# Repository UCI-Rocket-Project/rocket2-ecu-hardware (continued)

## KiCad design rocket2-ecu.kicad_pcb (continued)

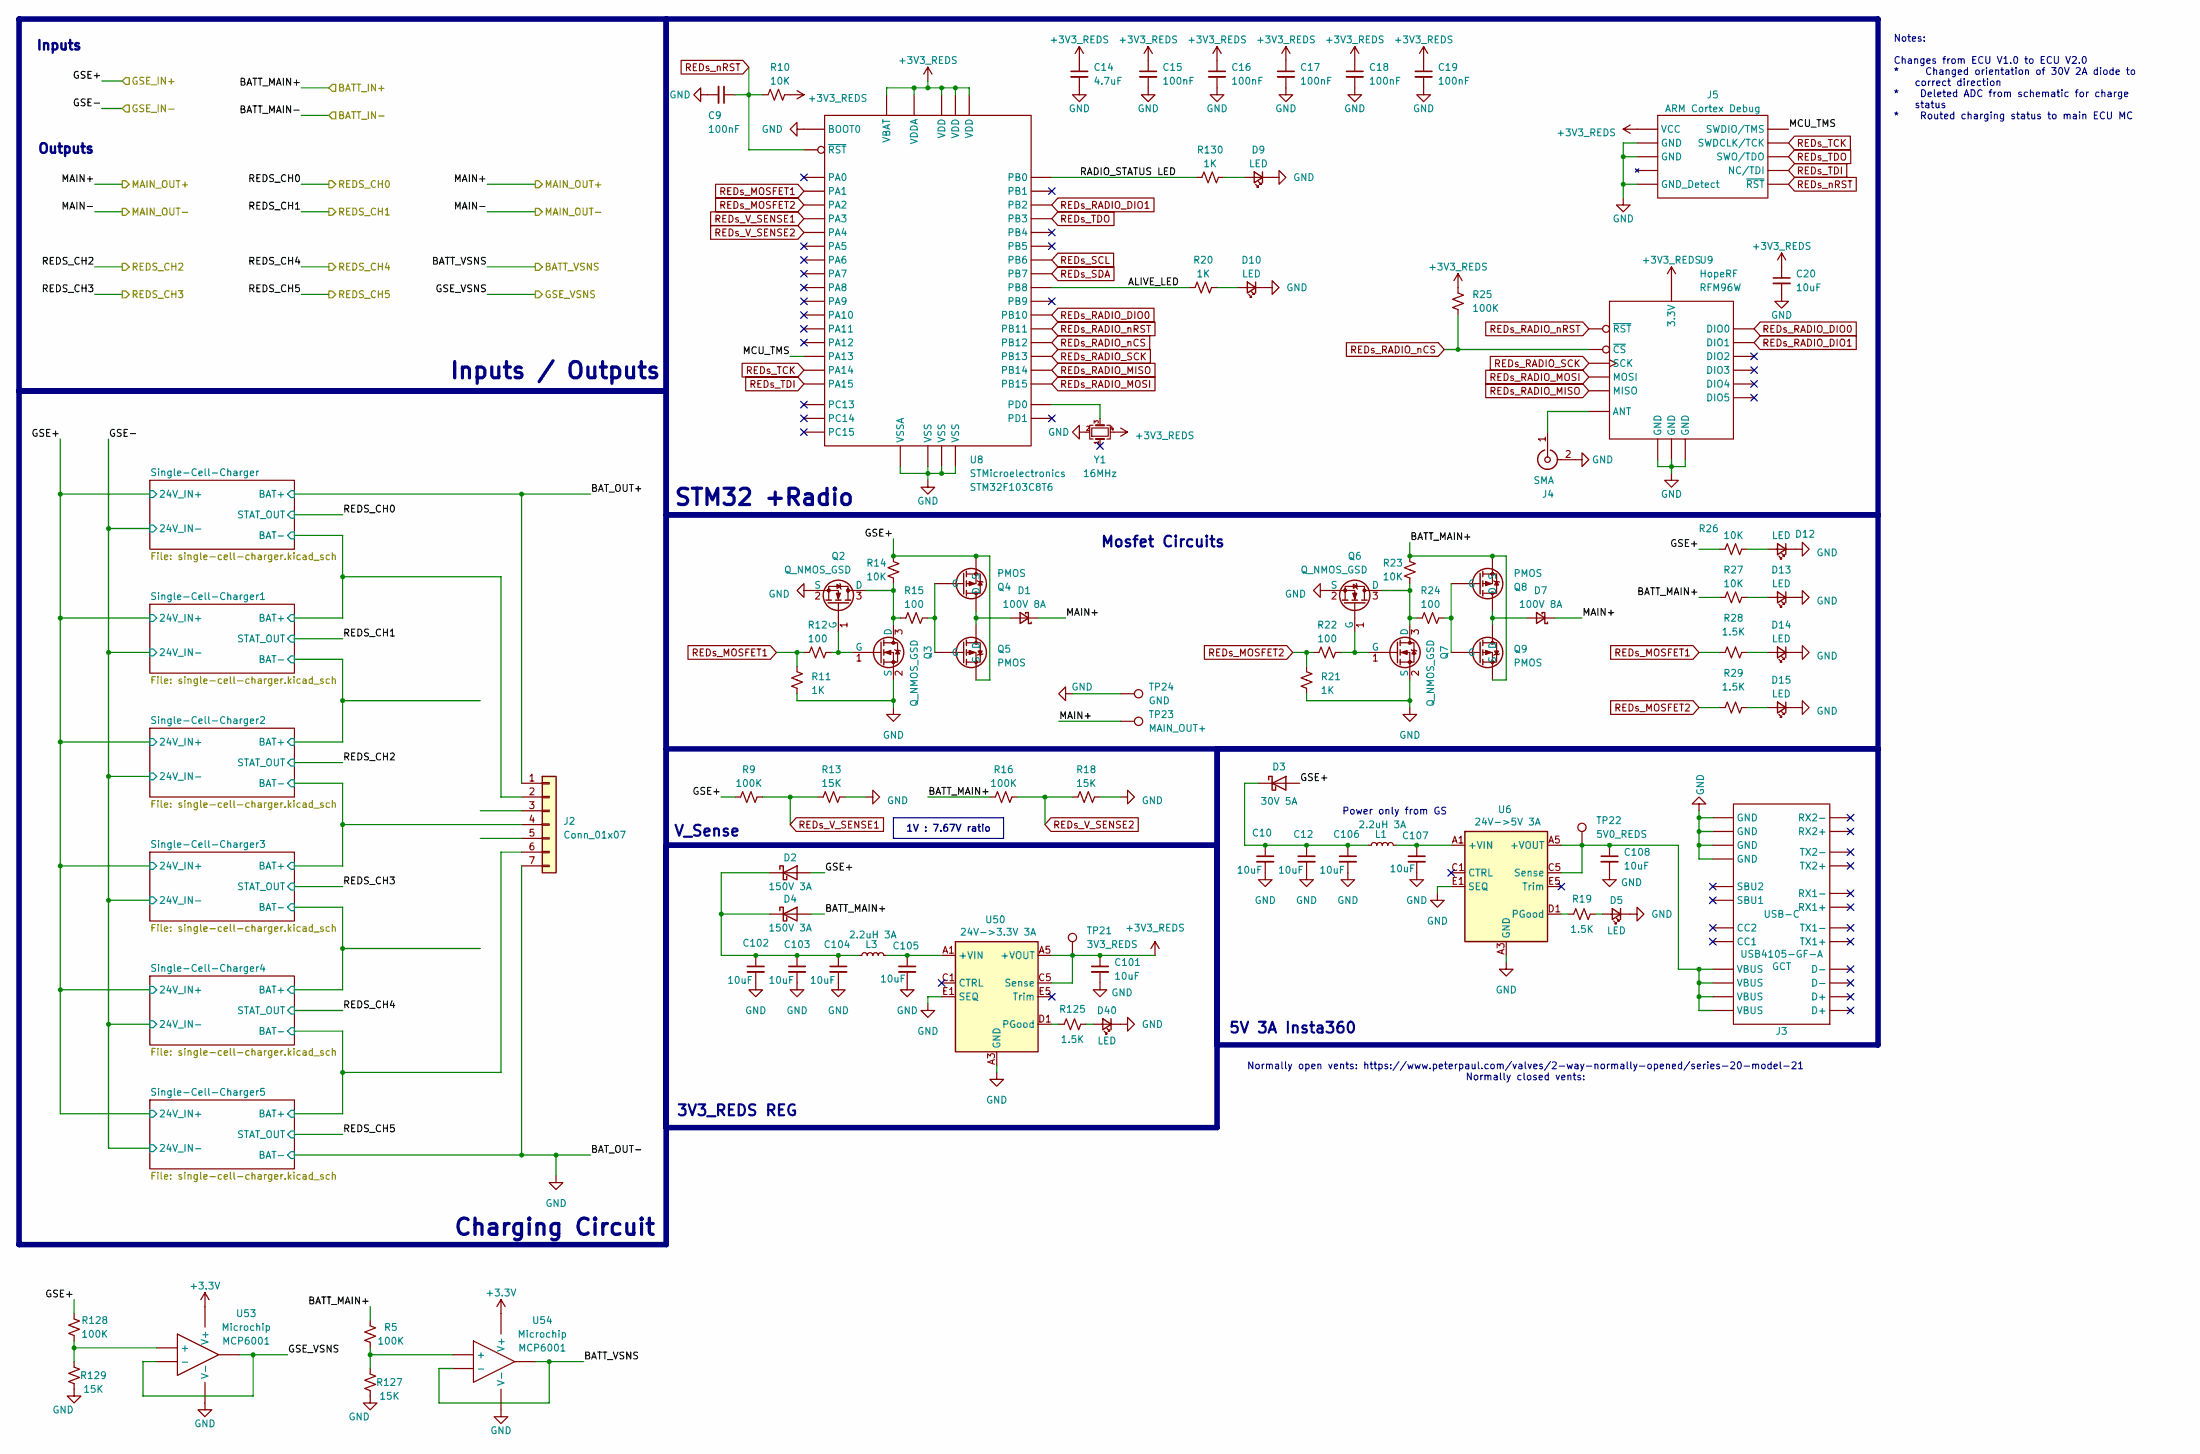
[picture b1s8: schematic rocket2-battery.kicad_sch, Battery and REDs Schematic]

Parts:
C9, C15, C16, C17, C18, C19: 100nF; C_0402_1005Metric; Part # Generic CAP CER 0.1UF 6.3V X7R 0402
C10, C12, C102, C103, C104, C105, C106, C107: 10uF; C_1210_3225Metric; Part # Generic CAP CER 10UF 50V X7R 1210
C14: 4.7uF; C_0603_1608Metric; Part # Generic CAP CER 4.7UF 6.3V X7R 0603
C20: 10uF; C_0603_1608Metric; Part # Generic CAP CER 10UF 50V X7R 0603
C101, C108: 10uF; C_1206_3216Metric; Part # Generic CAP CER 10UF 25V X7R 1206
D1, D7: 100V 8A; D_PowerDI-5; Part # SDT8A100P5-7
D2, D4: 150V 3A; D_SMF
D3: 30V 5A; D_SOD-128; Part # PMEG3050EP,115
D5, D40: LED; LED_0603_1608Metric_Pad1.05x0.95mm_HandSolder; Part # Generic 0603 Yellow-Green LED
D9, D10, D14, D15: LED; LED_0603_1608Metric_Pad1.05x0.95mm_HandSolder; Part # Generic 0603 Red LED
D12, D13: LED; LED_0603_1608Metric_Pad1.05x0.95mm_HandSolder; Part # Generic 0603 Green LED
J2: Conn_01x07; JST_PH_B7B-PH-K_1x07_P2.00mm_Vertical; Part # Generic 2.54mm 1x7 Pin Header
J3: USB-C; USB_C_Receptacle_GCT_USB4105-xx-A_16P_TopMnt_Horizontal; Part # USB4105-GF-A
J4: SMA; SMA_Molex_73251-2200_Horizontal; Part # 0732512200
J5: ARM Cortex Debug; PinHeader_2x05_P1.27mm_Vertical_SMD; Part # Generic 1.27mm 2x5 Pin Header
L1, L3: 2.2uH 3A; L_Vishay_IHLP-1212; Part # IHLP1212BZER2R2M11
Q2, Q3, Q6, Q7: Q_NMOS_GSD; SOT-23-3; Part # NTR4003NT3G
Q4, Q5, Q8, Q9: PMOS; Vishay_PowerPAK_1212-8_Single; Part # SI7315DN-T1-GE3
R5, R9, R16, R25, R128: 100K; R_0402_1005Metric; Part # Generic RES SMD 100K OHM 1% 1/16W 0402
R10, R14, R23, R26, R27: 10K; R_0402_1005Metric; Part # Generic RES SMD 10K OHM 1% 1/4W 0402
R11, R20, R21, R130: 1K; R_0402_1005Metric; Part # Generic RES SMD 1K OHM 1% 1/16W 0402
R12, R15, R22, R24: 100; R_0402_1005Metric; Part # Generic RES SMD 100 OHM 1% 1/4W 0402
R13, R18, R127, R129: 15K; R_0402_1005Metric; Part # Generic RES SMD 15K OHM 0.1% 1/16W 0402
R19, R28, R29, R125: 1.5K; R_0402_1005Metric; Part # Generic RES SMD 1.5K OHM 0.1% 1/16W 0402
TP21: 3V3_REDS; TestPoint_Plated_Hole_D2.0mm
TP22: 5V0_REDS; TestPoint_Plated_Hole_D2.0mm
TP23: MAIN_OUT+; TestPoint_Plated_Hole_D2.0mm
TP24: GND; TestPoint_Plated_Hole_D2.0mm
U6: 24V->5V 3A; Converter_DCDC_RECOM_RPMx.x-x.0; Part # RPMB5.0-3.0
U8: LQFP-48_7x7mm_P0.5mm; Part # STM32F103C8T6
U9: RFM95W; Part # RFM96W
U50: 24V->3.3V 3A; Converter_DCDC_RECOM_RPMx.x-x.0; Part # RPMB3.3-3.0
U53, U54: SOT-23-5; Part # MCP6001
Y1: 16MHz; Crystal_SMD_2520-4Pin_2.5x2.0mm; Part # ECS-2520MV-160-CN

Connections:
+3.3V: U53.5 (V+), U54.5 (V+); also elsewhere on the board
+3V3_REDS: C14.1, C15.1, C16.1, C17.1, C18.1, C19.1, C20.1, C101.1, J5.1 (VCC), R10.1, R25.1, TP21.1, U8.1 (VBAT), U8.9 (VDDA), U8.24 (VDD), U8.36 (VDD), U8.48 (VDD), U9.13 (3.3V), U50.A5 (+VOUT), U50.B5 (+VOUT), U50.C5 (Sense), Y1.4; also elsewhere on the board
+24V: D1.1 (K), D7.1 (K), TP23.1; also elsewhere on the board
/BATT: D4.2 (A), Q8.1 (S), Q8.2 (S), Q8.3 (S), Q9.1 (S), Q9.2 (S), Q9.3 (S), R5.1, R16.1, R23.1, R27.1; also elsewhere on the board
/GSE: D2.2 (A), D3.2 (A), Q4.1 (S), Q4.2 (S), Q4.3 (S), Q5.1 (S), Q5.2 (S), Q5.3 (S), R9.1, R14.1, R26.1, R128.1; also elsewhere on the board
/REDs/ALIVE_LED: R20.1, U8.45 (PB8)
/REDs/BATT_VSNS: U54.1, U54.4 (-)
/REDs/BAT_OUT+: J2.1; also elsewhere on the board
/REDs/GSE_VSNS: U53.1, U53.4 (-)
/REDs/MCU_TMS: J5.2 (SWDIO/TMS), U8.34 (PA13)
/REDs/RADIO_STATUS LED: R130.1, U8.18 (PB0)
/REDs/Single-Cell-Charger2/ISO_GND: J2.4; also elsewhere on the board
/REDs/Single-Cell-Charger4/ISO_GND: J2.6; also elsewhere on the board
/REDs/Single-Cell-Charger/ISO_GND: J2.2; also elsewhere on the board
GND: C9.2, C10.2, C12.2, C14.2, C15.2, C16.2, C17.2, C18.2, C19.2, C20.2, C101.2, C102.2, C103.2, C104.2, C105.2, C106.2, C107.2, C108.2, D5.1 (K), D9.1 (K), D10.1 (K), D12.1 (K), D13.1 (K), D14.1 (K), D15.1 (K), D40.1 (K), J2.7, J3.A1 (GND), J3.A12 (GND), J3.B1 (GND), J3.B12 (GND), J4.2 (Ext), J5.3 (GND), J5.5 (GND), J5.9 (GND_Detect), Q2.2 (S), Q3.2 (S), Q6.2 (S), Q7.2 (S), R11.1, R13.2, R18.2, R21.1, R127.2, R129.2, TP24.1, U6.A3 (GND), U6.A4 (GND), U6.B1 (GND), U6.B2 (GND), U6.B3 (GND), U6.B4 (GND), U6.C2 (GND), U6.C3 (GND), U6.C4 (GND), U6.D2 (GND), U6.D3 (GND), U6.D4 (GND), U6.D5 (GND), U6.E1 (SEQ), U6.E3 (GND), U6.E4 (GND), U8.8 (VSSA), U8.23 (VSS), U8.35 (VSS), U8.44 (BOOT0), U8.47 (VSS), U9.1 (GND), U9.8 (GND), U9.10 (GND), U50.A3 (GND), U50.A4 (GND), U50.B1 (GND), U50.B2 (GND), U50.B3 (GND), U50.B4 (GND), U50.C2 (GND), U50.C3 (GND), U50.C4 (GND), U50.D2 (GND)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; also elsewhere on the board
unnamed: C105.1, L3.2, U50.A1 (+VIN), U50.A2 (+VIN)
unnamed: C107.1, L1.2, U6.A1 (+VIN), U6.A2 (+VIN)
unnamed: D1.2 (A), Q4.5 (D), Q5.5 (D)
unnamed: C102.1, C103.1, C104.1, D2.1 (K), D4.1 (K), L3.1
unnamed: C10.1, C12.1, C106.1, D3.1 (K), L1.1
unnamed: D5.2 (A), R19.2
unnamed: D7.2 (A), Q8.5 (D), Q9.5 (D)
unnamed: D9.2 (A), R130.2
unnamed: D10.2 (A), R20.2
unnamed: D12.2 (A), R26.2
unnamed: D13.2 (A), R27.2
unnamed: D14.2 (A), R28.2
unnamed: D15.2 (A), R29.2
unnamed: D40.2 (A), R125.2
unnamed: J4.1 (In), U9.9 (ANT)
unnamed: Q2.3 (D), Q3.3 (D), R14.2, R15.1
unnamed: Q2.1 (G), Q3.1 (G), R12.2
unnamed: Q4.4 (G), Q5.4 (G), R15.2
unnamed: Q6.3 (D), Q7.3 (D), R23.2, R24.1
unnamed: Q6.1 (G), Q7.1 (G), R22.2
unnamed: Q8.4 (G), Q9.4 (G), R24.2
unnamed: R19.1, U6.D1 (PGood)
unnamed: C108.1, J3.A4 (VBUS), J3.A9 (VBUS), J3.B4 (VBUS), J3.B9 (VBUS), TP22.1, U6.A5 (+VOUT), U6.B5 (+VOUT), U6.C5 (Sense)
unnamed: U8.5 (PD0), Y1.3
unnamed: R125.1, U50.D1 (PGood)
unnamed: R128.2, R129.1, U53.3 (+)
unnamed: R5.2, R127.1, U54.3 (+)
REDs_MOSFET1: R11.2, R12.1, R28.1, U8.11 (PA1)
REDs_MOSFET2: R21.2, R22.1, R29.1, U8.12 (PA2)
REDs_RADIO_DIO0: U8.21 (PB10), U9.14 (DIO0)
REDs_RADIO_DIO1: U8.20 (PB2), U9.15 (DIO1)
REDs_RADIO_MISO: U8.27 (PB14), U9.2 (MISO)
REDs_RADIO_MOSI: U8.28 (PB15), U9.3 (MOSI)
REDs_RADIO_SCK: U8.26 (PB13), U9.4 (SCK)
REDs_RADIO_nCS: R25.2, U8.25 (PB12), U9.5 (~CS)
REDs_RADIO_nRST: U8.22 (PB11), U9.6 (~RST)
REDs_SCL: U8.42 (PB6)
REDs_SDA: U8.43 (PB7)
REDs_TCK: J5.4 (SWDCLK/TCK), U8.37 (PA14)
REDs_TDI: J5.8 (NC/TDI), U8.38 (PA15)
REDs_TDO: J5.6 (SWO/TDO), U8.39 (PB3)
REDs_V_SENSE1: R9.2, R13.1, U8.13 (PA3)
REDs_V_SENSE2: R16.2, R18.1, U8.14 (PA4)
REDs_nRST: C9.1, J5.10 (~RST), R10.2, U8.7 (~RST)

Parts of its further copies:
C8: 100nF; C_0402_1005Metric; Part # Generic CAP CER 0.1UF 6.3V X7R 0402

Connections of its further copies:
+3.3V: C8.1; also elsewhere on the board
GND: C8.2; also elsewhere on the board

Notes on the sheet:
Inputs
Outputs
STM32 +Radio
Inputs / Outputs
5V 3A Insta360
Normally open vents: https://www.peterpaul.com/valves/2-way-normally-opened/series-20-model-21 Normally closed vents:
Power only from GS
Notes: Changes from ECU V1.0 to ECU V2.0 * Changed orientation of 30V 2A diode to correct direction * Deleted ADC from schematic for charge status * Routed charging status to main ECU MC
Charging Circuit
3V3_REDS REG
Mosfet Circuits
V_Sense
1V : 7.67V ratio

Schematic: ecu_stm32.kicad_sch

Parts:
C59, C60, C61, C62, C63, C64, C65, C66, C67, C68, C70, C71, C72, C74, C75, C77, C78, C79, C80, C81, C82, C83, C84, C88, C89: 100nF; C_0402_1005Metric; Part # Generic CAP CER 0.1UF 6.3V X7R 0402
C69, C73, C90: 2.2uF; C_0603_1608Metric; Part # Generic CAP CER 2.2UF 6.3V X7R 0603
C76: 10uF; C_0603_1608Metric; Part # Generic CAP CER 10UF 50V X7R 0603
C85, C87: 1uF; C_0603_1608Metric; Part # Generic CAP CER 1UF 50V X7R 0603
C86: 4.7uF; C_0603_1608Metric; Part # Generic CAP CER 4.7UF 6.3V X7R 0603
D34, D35: 6.8V; D_0402_1005Metric; Part # ESD321DPYR
D36: LED; LED_0603_1608Metric_Pad1.05x0.95mm_HandSolder; Part # Generic 0603 Red LED
J16: USB-C; USB_C_Receptacle_GCT_USB4105-xx-A_16P_TopMnt_Horizontal; Part # USB4105-GF-A
J17: ARM Cortex Debug; PinHeader_2x05_P1.27mm_Vertical_SMD; Part # Generic 1.27mm 2x5 Pin Header
R103, R104, R107, R108: 10K; R_0402_1005Metric; Part # Generic RES SMD 10K OHM 1% 1/4W 0402
R105, R106: 5.1K; R_0603_1608Metric_Pad0.98x0.95mm_HandSolder; Part # Generic RES SMD 5.1K OHM 1% 1/16W 0402
R109: 100; R_0402_1005Metric; Part # Generic RES SMD 100 OHM 1% 1/4W 0402
U40: LQFP-176_24x24mm_P0.5mm; Part # STM32F469IIT6
Y2: 16MHz; Crystal_SMD_2016-4Pin_2.0x1.6mm; Part # ECS-1633-160-BN-TR

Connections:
+3.3V: C59.2, C60.2, C61.2, C62.2, C63.2, C64.2, C65.2, C66.2, C67.2, C68.2, C70.2, C71.2, C74.2, C75.2, C77.2, C78.2, C79.2, C80.2, C81.2, C82.2, C83.2, C84.2, C85.2, C86.2, C87.2, C88.2, C89.1, J17.1 (VCC), R103.1, R104.2, U40.6 (VBAT), U40.15 (VDD), U40.23 (VDD), U40.36 (VDD), U40.38 (VREF), U40.39 (VDDA), U40.49 (VDD), U40.62 (VDD), U40.72 (VDD), U40.82 (VDD), U40.96 (VDD), U40.118 (VDDUSB), U40.131 (VDD), U40.136 (VDD), U40.149 (VDD), U40.159 (VDD), U40.172 (VDD), Y2.4; also elsewhere on the board
ALARM: U40.70 (PE9); also elsewhere on the board
ALT_MISO: U40.4 (PE5); also elsewhere on the board
ALT_MOSI: U40.5 (PE6); also elsewhere on the board
ALT_SCK: U40.1 (PE2); also elsewhere on the board
ALT_nCS: U40.2 (PE3); also elsewhere on the board
ECU_BV: U40.50 (PA4)
ECU_GS: U40.19 (PF3)
ETH_CP2: U40.88 (PB15); also elsewhere on the board
ETH_CTS: U40.86 (PB13); also elsewhere on the board
ETH_RTS: U40.87 (PB14); also elsewhere on the board
ETH_RX: U40.79 (PB10); also elsewhere on the board
ETH_TX: U40.80 (PB11); also elsewhere on the board
ETH_nRST: U40.85 (PB12); also elsewhere on the board
GND: C59.1, C60.1, C61.1, C62.1, C63.1, C64.1, C65.1, C66.1, C67.1, C68.1, C69.1, C70.1, C71.1, C72.2, C73.1, C74.1, C75.1, C76.2, C77.1, C78.1, C79.1, C80.1, C81.1, C82.1, C83.1, C84.1, C85.1, C86.1, C87.1, C88.1, C89.2, C90.1, D34.2 (A), D35.2 (A), D36.1 (K), J16.A1 (GND), J16.A12 (GND), J16.B1 (GND), J16.B12 (GND), J17.3 (GND), J17.5 (GND), J17.9 (GND_Detect), R105.2, R106.2, R108.2, U40.14 (VSS), U40.22 (VSS), U40.37 (VSSA), U40.48 (BYPASS_REG), U40.61 (VSS), U40.71 (VSS), U40.95 (VSS), U40.99 (VDDDSI), U40.103 (VSSDSI), U40.109 (VSSDSI), U40.117 (VSS), U40.130 (VSS), U40.135 (VSS), U40.148 (VSS), U40.158 (VSS), U40.166 (BOOT0), Y2.2; also elsewhere on the board
GPS_INT: U40.43 (PH2); also elsewhere on the board
GPS_RX: U40.40 (PA0); also elsewhere on the board
GPS_TX: U40.41 (PA1); also elsewhere on the board
IMU_INT1: U40.151 (PD7); also elsewhere on the board
IMU_INT2: U40.152 (PG9); also elsewhere on the board
IMU_INT3: U40.150 (PD6); also elsewhere on the board
IMU_INT4: U40.147 (PD5); also elsewhere on the board
IMU_MISO: U40.155 (PG12); also elsewhere on the board
IMU_MOSI: U40.157 (PG14); also elsewhere on the board
IMU_SCK: U40.156 (PG13); also elsewhere on the board
IMU_nCS1: U40.154 (PG11); also elsewhere on the board
IMU_nCS2: U40.153 (PG10); also elsewhere on the board
MAG_INT: U40.164 (PB6); also elsewhere on the board
MAG_SCL: U40.167 (PB8); also elsewhere on the board
MAG_SDA: U40.165 (PB7); also elsewhere on the board
MCU_TCK: J17.4 (SWDCLK/TCK), U40.137 (PA14)
MCU_TDI: J17.8 (NC/TDI), U40.138 (PA15)
MCU_TDO: J17.6 (SWO/TDO), U40.161 (PB3)
MCU_TMS: J17.2 (SWDIO/TMS), U40.128 (PA13)
MCU_nRST: C72.1, J17.10 (~RST), R103.2, U40.31 (~RST)
MEM1_nCS: U40.59 (PF11); also elsewhere on the board
MEM_MISO: U40.52 (PA6); also elsewhere on the board
MEM_MOSI: U40.53 (PA7); also elsewhere on the board
MEM_SCK: U40.51 (PA5); also elsewhere on the board
MEM_nCS: U40.44 (PH3); also elsewhere on the board
unnamed: D36.2 (A), R109.1
unnamed: J16.A5 (CC1), R105.1
unnamed: J16.B5 (CC2), R106.1
unnamed: R104.1, U40.171 (PDR_ON)
unnamed: C73.2, U40.81 (VCAP1)
unnamed: C69.2, U40.129 (VCAP2)
unnamed: U40.29 (PH0), Y2.3
unnamed: C90.2, U40.100 (VCAPDSI), U40.106 (VDD12DSI)
PT0: U40.28 (PF10); also elsewhere on the board
PT1: U40.32 (PC0); also elsewhere on the board
PT2: U40.33 (PC1); also elsewhere on the board
PT3: U40.34 (PC2); also elsewhere on the board
PT4: U40.35 (PC3); also elsewhere on the board
PT5: U40.42 (PA2); also elsewhere on the board
PT6: U40.47 (PA3)
RADIO1_DIO1: U40.18 (PF2); also elsewhere on the board
RADIO1_nCS: U40.20 (PF4); also elsewhere on the board
RADIO1_nRST: U40.21 (PF5); also elsewhere on the board
RADIO2_DIO0: U40.12 (PI10)
RADIO2_DIO1: U40.11 (PI9)
RADIO2_nCS: U40.10 (PC15)
RADIO2_nRST: U40.9 (PC14)
RADIO_DIO0: U40.17 (PF1); also elsewhere on the board
RADIO_DIO1: U40.16 (PF0); also elsewhere on the board
RADIO_MISO: U40.26 (PF8); also elsewhere on the board
RADIO_MOSI: U40.27 (PF9); also elsewhere on the board
RADIO_SCK: U40.25 (PF7); also elsewhere on the board
RADIO_nCS: U40.24 (PF6); also elsewhere on the board
RADIO_nRST: U40.13 (PI11); also elsewhere on the board
SOLENOID0_EN: U40.63 (PF13); also elsewhere on the board
SOLENOID0_FB: U40.54 (PC4); also elsewhere on the board
SOLENOID1_EN: U40.64 (PF14); also elsewhere on the board
SOLENOID1_FB: U40.55 (PC5); also elsewhere on the board
SOLENOID2_EN: U40.65 (PF15); also elsewhere on the board
SOLENOID2_FB: U40.56 (PB0); also elsewhere on the board
SOLENOID3_EN: U40.66 (PG0); also elsewhere on the board
SOLENOID3_FB: U40.57 (PB1); also elsewhere on the board
STATUS_LED: R109.2, U40.113 (PG5)
TC0_MISO: U40.140 (PC11); also elsewhere on the board
TC0_SCK: U40.139 (PC10); also elsewhere on the board
TC0_nCS: U40.141 (PC12); also elsewhere on the board
TC1_nCS: U40.142 (PD0); also elsewhere on the board
USB_CONN_D+: D34.1 (K), J16.A6 (D+), J16.B6 (D+), U40.127 (PA12)
USB_CONN_D-: D35.1 (K), J16.A7 (D-), J16.B7 (D-), U40.126 (PA11)
USB_VBUS: C76.1, J16.A4 (VBUS), J16.A9 (VBUS), J16.B4 (VBUS), J16.B9 (VBUS), R107.1
USB_VBUS_SENS: R107.2, R108.1, U40.124 (PA9)

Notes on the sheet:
POWER SUPPLY SCHEME
PIN ASSIGNMENTS
USB-C + SWD
IN IOC PH1 is OSC OUT
For VDDUSB
LC Filter?
For VDDA
PWM Configurable from 0-255
For Crystal Oscillator
For VREF
For VDD

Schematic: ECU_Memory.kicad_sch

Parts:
C96, C97: 100nF; C_0402_1005Metric; Part # Generic CAP CER 0.1UF 6.3V X7R 0402
R119, R120: 100K; R_0402_1005Metric; Part # Generic RES SMD 100K OHM 1% 1/16W 0402
U46, U47: WSON-8-1EP_8x6mm_P1.27mm_EP3.4x4.3mm; Part # W25N01GVZEIG TR

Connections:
+3.3V: C96.1, C97.1, R119.1, R120.1, U46.3 (~WP), U46.7 (~HOLD), U46.8 (VDD), U47.3 (~WP), U47.7 (~HOLD), U47.8 (VDD); also elsewhere on the board
GND: C96.2, C97.2, U46.4 (VSS), U47.4 (VSS); also elsewhere on the board
MEM1_nCS: R120.2, U47.1 (~CE); also elsewhere on the board
MEM_MISO: U46.2 (SO), U47.2 (SO); also elsewhere on the board
MEM_MOSI: U46.5 (SI), U47.5 (SI); also elsewhere on the board
MEM_SCK: U46.6 (SCK), U47.6 (SCK); also elsewhere on the board
MEM_nCS: R119.2, U46.1 (~CE); also elsewhere on the board

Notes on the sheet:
1GB

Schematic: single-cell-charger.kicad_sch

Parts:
C21, C23: 1uF; C_0603_1608Metric; Part # Generic CAP CER 1UF 50V X7R 0603
C22: 10uF; C_0603_1608Metric; Part # Generic CAP CER 10UF 50V X7R 0603
D16, D43: LED; LED_0603_1608Metric_Pad1.05x0.95mm_HandSolder; Part # Generic 0603 Blue LED
R30: 27K; R_0603_1608Metric; Part # CR0603-FX-2702ELF
R31: 375; R_0402_1005Metric; Part # Generic RES SMD 375 OHM 0.1% 1/16W 0402
R32, R33, R34: 10K; R_0402_1005Metric; Part # Generic RES SMD 10K OHM 1% 1/4W 0402
R35: 1K; R_0402_1005Metric; Part # Generic RES SMD 1K OHM 1% 1/16W 0402
R36: 1.5K; R_0402_1005Metric; Part # Generic RES SMD 1.5K OHM 0.1% 1/16W 0402
TP1: ISO_5V; TestPoint_Plated_Hole_D2.0mm
TP7: BAT+; TestPoint_Plated_Hole_D2.0mm
U10: EC4SAW-xxSxxN; Part # EC4SAW-xxSxxN
U11: WSON-8-1EP_2x2mm_P0.5mm_EP0.9x1.6mm; Part # BQ25170
U12: VOS615A-1; SOP-4_4.4x2.6mm_P1.27mm; Part # VOS615A-1X001T

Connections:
+3V3_REDS: R36.1; also elsewhere on the board
/GSE: U10.2 (VIN+); also elsewhere on the board
/REDs/BAT_OUT+: C23.2, TP7.1, U11.8 (OUT); also elsewhere on the board
/REDs/REDS_CH0: R36.2, U12.4
/REDs/Single-Cell-Charger/ISO_5V: C21.1, C22.1, R33.2, R34.2, TP1.1, U10.6 (VOUT+), U11.1 (IN), U12.1
/REDs/Single-Cell-Charger/ISO_GND: C21.2, C22.2, C23.1, R30.2, R31.1, R32.2, U10.7 (VOUT-), U11.4 (GND), U11.9 (GND); also elsewhere on the board
/REDs/Single-Cell-Charger/stat: D16.1 (K), R35.2, U11.5 (STAT)
GND: U10.1 (VIN-), U12.3; also elsewhere on the board
unnamed: D16.2 (A), R34.1
unnamed: D43.2 (A), R33.1
unnamed: D43.1 (K), U11.6 (~PG)
unnamed: R35.1, U12.2
unnamed: R31.2, U11.2 (ISET)
unnamed: R32.1, U11.3 (TS)
unnamed: R30.1, U11.7 (VSET)

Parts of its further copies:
C25, C28, C31, C34, C37: 10uF; C_0603_1608Metric; Part # Generic CAP CER 10UF 50V X7R 0603
C26, C29, C30, C32, C33, C35, C36, C38: 1uF; C_0603_1608Metric; Part # Generic CAP CER 1UF 50V X7R 0603
D17, D18, D19, D20, D21, D44, D45, D46, D47, D48: LED; LED_0603_1608Metric_Pad1.05x0.95mm_HandSolder; Part # Generic 0603 Blue LED
R38, R45, R52, R59, R66: 375; R_0402_1005Metric; Part # Generic RES SMD 375 OHM 0.1% 1/16W 0402
R39, R46, R48, R53, R54, R55, R60, R61, R62, R67, R68, R69: 10K; R_0402_1005Metric; Part # Generic RES SMD 10K OHM 1% 1/4W 0402
R42, R56, R63, R70: 1K; R_0402_1005Metric; Part # Generic RES SMD 1K OHM 1% 1/16W 0402
R44, R51, R58, R65: 27K; R_0603_1608Metric; Part # CR0603-FX-2702ELF
R57, R64, R71: 1.5K; R_0402_1005Metric; Part # Generic RES SMD 1.5K OHM 0.1% 1/16W 0402
TP2, TP3, TP4, TP5, TP6: ISO_5V; TestPoint_Plated_Hole_D2.0mm
TP8, TP9, TP10, TP11, TP12: BAT+; TestPoint_Plated_Hole_D2.0mm
U13, U14, U17, U20, U23, U26: WSON-8-1EP_2x2mm_P0.5mm_EP0.9x1.6mm; Part # BQ25170
U16, U19, U22, U25: EC4SAW-xxSxxN; Part # EC4SAW-xxSxxN
U18, U21, U24, U27: VOS615A-1; SOP-4_4.4x2.6mm_P1.27mm; Part # VOS615A-1X001T

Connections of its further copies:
+3V3_REDS: R57.1, R64.1, R71.1; also elsewhere on the board
/GSE: U13.2 (VIN+), U16.2 (VIN+), U19.2 (VIN+), U22.2 (VIN+), U25.2 (VIN+); also elsewhere on the board
/REDs/REDS_CH2: U18.4; also elsewhere on the board
/REDs/REDS_CH3: R57.2, U21.4
/REDs/REDS_CH4: R64.2, U24.4
/REDs/REDS_CH5: R71.2, U27.4
/REDs/Single-Cell-Charger1/ISO_5V: C25.1, TP2.1, U13.6 (VOUT+), U14.1 (IN); also elsewhere on the board
/REDs/Single-Cell-Charger1/ISO_GND: C25.2, C26.1, C29.2, R38.1, R39.2, TP9.1, U13.7 (VOUT-), U14.4 (GND), U14.9 (GND), U17.8 (OUT); also elsewhere on the board
/REDs/Single-Cell-Charger1/stat: D17.1 (K), R42.2, U14.5 (STAT)
/REDs/Single-Cell-Charger2/ISO_5V: C28.1, R48.2, TP3.1, U16.6 (VOUT+), U17.1 (IN), U18.1; also elsewhere on the board
/REDs/Single-Cell-Charger2/ISO_GND: C28.2, C29.1, C32.2, R44.2, R45.1, R46.2, TP10.1, U16.7 (VOUT-), U17.4 (GND), U17.9 (GND), U20.8 (OUT); also elsewhere on the board
/REDs/Single-Cell-Charger2/stat: D18.1 (K), U17.5 (STAT); also elsewhere on the board
/REDs/Single-Cell-Charger3/ISO_5V: C30.1, C31.1, R54.2, R55.2, TP4.1, U19.6 (VOUT+), U20.1 (IN), U21.1
/REDs/Single-Cell-Charger3/ISO_GND: C30.2, C31.2, C32.1, C35.2, R51.2, R52.1, R53.2, TP11.1, U19.7 (VOUT-), U20.4 (GND), U20.9 (GND), U23.8 (OUT)
/REDs/Single-Cell-Charger3/stat: D19.1 (K), R56.2, U20.5 (STAT)
/REDs/Single-Cell-Charger4/ISO_5V: C33.1, C34.1, R61.2, R62.2, TP5.1, U22.6 (VOUT+), U23.1 (IN), U24.1
/REDs/Single-Cell-Charger4/ISO_GND: C33.2, C34.2, C35.1, C38.2, R58.2, R59.1, R60.2, TP12.1, U22.7 (VOUT-), U23.4 (GND), U23.9 (GND), U26.8 (OUT); also elsewhere on the board
/REDs/Single-Cell-Charger4/stat: D20.1 (K), R63.2, U23.5 (STAT)
/REDs/Single-Cell-Charger5/ISO_5V: C36.1, C37.1, R68.2, R69.2, TP6.1, U25.6 (VOUT+), U26.1 (IN), U27.1
/REDs/Single-Cell-Charger5/stat: D21.1 (K), R70.2, U26.5 (STAT)
/REDs/Single-Cell-Charger/ISO_GND: C26.2, TP8.1, U14.8 (OUT); also elsewhere on the board
GND: C36.2, C37.2, C38.1, R65.2, R66.1, R67.2, U13.1 (VIN-), U16.1 (VIN-), U18.3, U19.1 (VIN-), U21.3, U22.1 (VIN-), U24.3, U25.1 (VIN-), U25.7 (VOUT-), U26.4 (GND), U26.9 (GND), U27.3; also elsewhere on the board
unnamed 97: D17.2 (A); also elsewhere on the board
unnamed: D18.2 (A), R48.1
unnamed: D19.2 (A), R55.1
unnamed: D20.2 (A), R62.1
unnamed: D21.2 (A), R69.1
unnamed 122: D44.2 (A); also elsewhere on the board
unnamed: D44.1 (K), U14.6 (~PG)
unnamed 124: D45.2 (A); also elsewhere on the board
unnamed: D45.1 (K), U17.6 (~PG)
unnamed: D46.2 (A), R54.1
unnamed: D46.1 (K), U20.6 (~PG)
unnamed: D47.2 (A), R61.1
unnamed: D47.1 (K), U23.6 (~PG)
unnamed: D48.2 (A), R68.1
unnamed: D48.1 (K), U26.6 (~PG)
unnamed 163: R42.1; also elsewhere on the board
unnamed 164: U18.2; also elsewhere on the board
unnamed: R56.1, U21.2
unnamed: R63.1, U24.2
unnamed: R70.1, U27.2
unnamed: R38.2, U14.2 (ISET)
unnamed: R39.1, U14.3 (TS)
unnamed 183: U14.7 (VSET); also elsewhere on the board
unnamed: R45.2, U17.2 (ISET)
unnamed: R46.1, U17.3 (TS)
unnamed: R44.1, U17.7 (VSET)
unnamed: R52.2, U20.2 (ISET)
unnamed: R53.1, U20.3 (TS)
unnamed: R51.1, U20.7 (VSET)
unnamed: R59.2, U23.2 (ISET)
unnamed: R60.1, U23.3 (TS)
unnamed: R58.1, U23.7 (VSET)
unnamed: R66.2, U26.2 (ISET)
unnamed: R67.1, U26.3 (TS)
unnamed: R65.1, U26.7 (VSET)

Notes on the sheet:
remove if fail
ctr is 0.5 os 0.5*4ma = 2ma vcc - vout = 3.3 - 0.8 = 2.5 2.5V / 2ma = 1250 = ~1.5k
~4mA Max Sink is 5mA
±1% tolerance resistor with <200 ppm/ºC

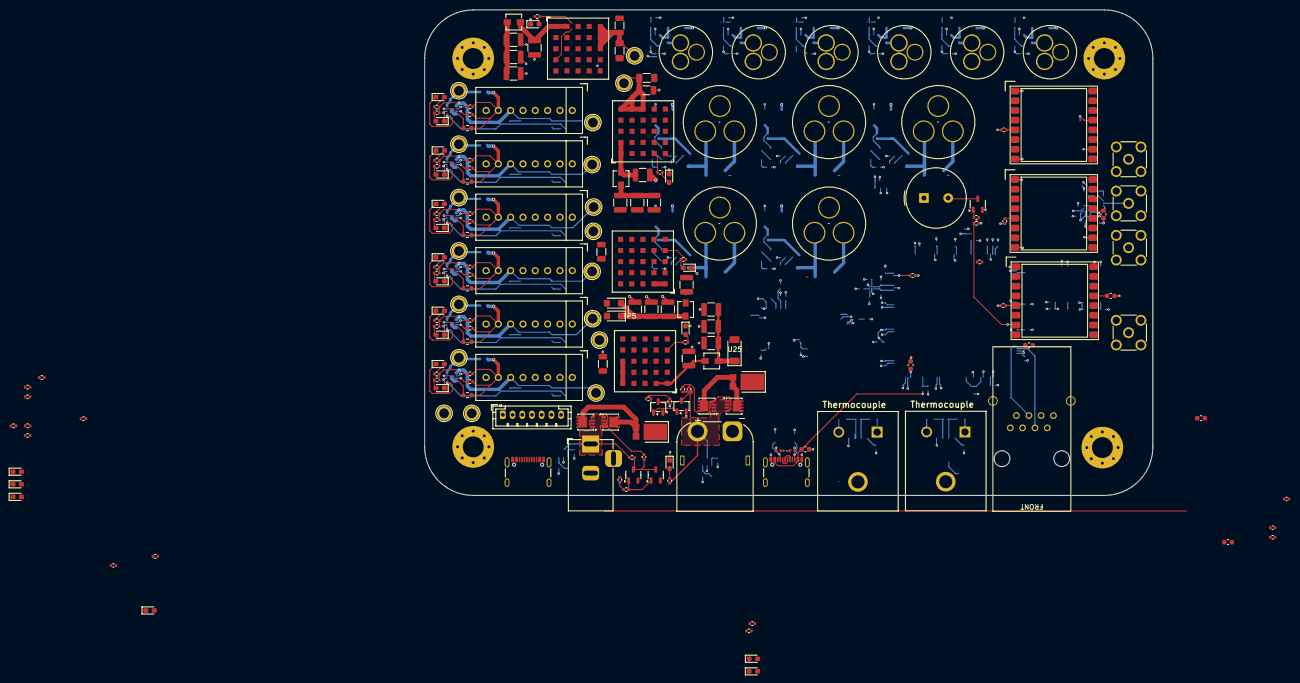
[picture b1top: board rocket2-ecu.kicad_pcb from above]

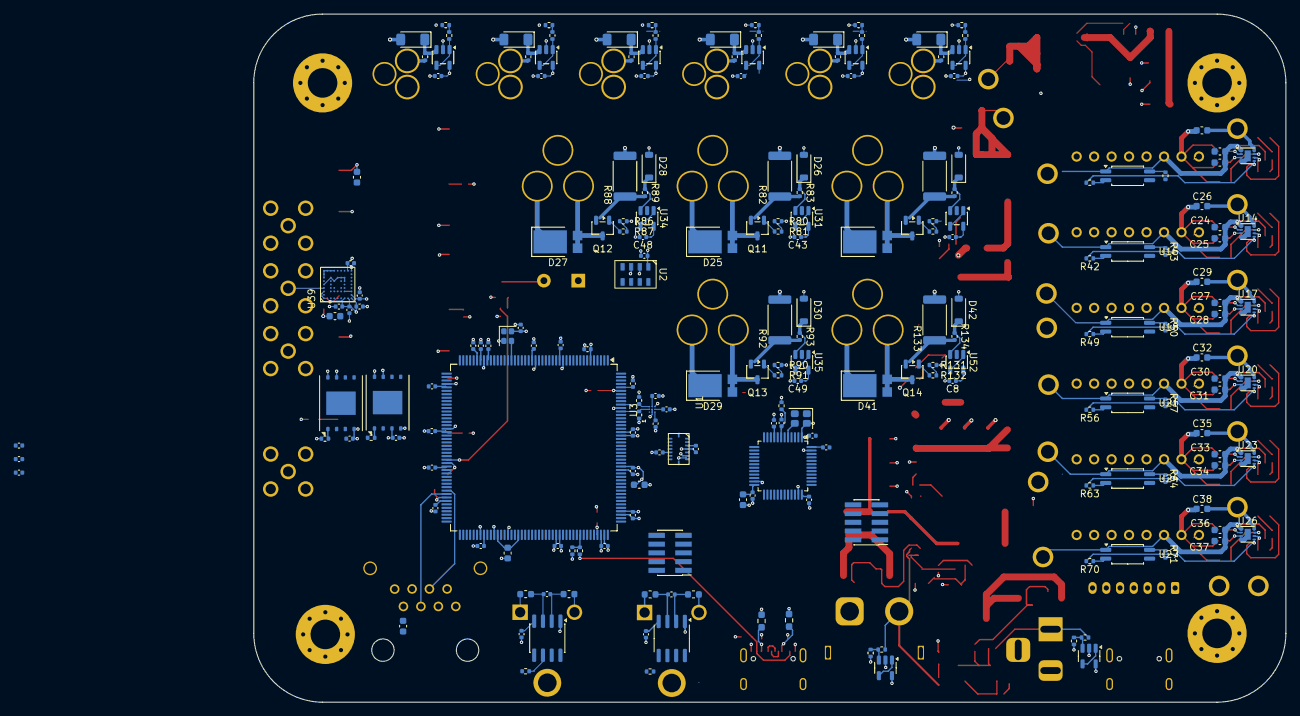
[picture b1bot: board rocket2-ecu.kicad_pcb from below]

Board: 6 copper layers, 150.0 x 100.0 mm, 403 parts (208 on the bottom side), 257 nets.

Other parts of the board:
C24, C27: 1uF; C_0603_1608Metric
R37: 27K; R_0603_1608Metric
R40, R41, R47: 10K; R_0402_1005Metric
R43, R50: 1.5K; R_0402_1005Metric
R49: 1K; R_0402_1005Metric
U15: VOS615A-1; SOP-4_4.4x2.6mm_P1.27mm

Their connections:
+3V3_REDS: R43.1, R50.1; also elsewhere on the board
/REDs/REDS_CH1: R43.2, U15.4
/REDs/REDS_CH2: R50.2; also elsewhere on the board
/REDs/Single-Cell-Charger1/ISO_5V: C24.1, R40.2, R41.2, U15.1; also elsewhere on the board
/REDs/Single-Cell-Charger1/ISO_GND: C24.2, R37.2; also elsewhere on the board
/REDs/Single-Cell-Charger2/ISO_5V: C27.1, R47.2; also elsewhere on the board
/REDs/Single-Cell-Charger2/ISO_GND: C27.2; also elsewhere on the board
/REDs/Single-Cell-Charger2/stat: R49.2; also elsewhere on the board
GND: U15.3; also elsewhere on the board
unnamed 97: R41.1; also elsewhere on the board
unnamed 122: R40.1; also elsewhere on the board
unnamed 124: R47.1; also elsewhere on the board
unnamed 163: U15.2; also elsewhere on the board
unnamed 164: R49.1; also elsewhere on the board
unnamed 183: R37.1; also elsewhere on the board

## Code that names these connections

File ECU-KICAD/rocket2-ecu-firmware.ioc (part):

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Mcu.Name=STM32F469IITx
Mcu.Package=LQFP176
Mcu.UserName=STM32F469IITx
PA0/WKUP.GPIOParameters=GPIO_Label
PA0/WKUP.GPIO_Label=GPS_TX
PA0/WKUP.Mode=Asynchronous
PA0/WKUP.Signal=UART4_TX
PA1.GPIOParameters=GPIO_Label
PA1.GPIO_Label=GPS_RX
PA1.Mode=Asynchronous
PA1.Signal=UART4_RX
PA11.GPIOParameters=GPIO_Label
PA11.GPIO_Label=USB_CONN_D-
PA11.Mode=Device_Only
PA11.Signal=USB_OTG_FS_DM
PA12.GPIOParameters=GPIO_Label
PA12.GPIO_Label=USB_CONN_D+
PA12.Mode=Device_Only
PA12.Signal=USB_OTG_FS_DP
PA13.GPIOParameters=GPIO_Label
PA13.GPIO_Label=MCU_TMS
PA13.Mode=JTAG_4_pins
PA13.Signal=SYS_JTMS-SWDIO
PA14.GPIOParameters=GPIO_Label
PA14.GPIO_Label=MCU_TCK
PA14.Mode=JTAG_4_pins
PA14.Signal=SYS_JTCK-SWCLK
PA15.GPIOParameters=GPIO_Label
PA15.GPIO_Label=MCU_TDI
PA15.Mode=JTAG_4_pins
PA15.Signal=SYS_JTDI
PA3.GPIOParameters=GPIO_Label
PA3.GPIO_Label=PT3
PA3.Signal=ADCx_IN3
PA4.GPIOParameters=GPIO_Label
PA4.GPIO_Label=ECU_BV
PA4.Signal=ADCx_IN4
PA5.GPIOParameters=GPIO_Label
PA5.GPIO_Label=MEM_SCK
PA5.Mode=Full_Duplex_Master
PA5.Signal=SPI1_SCK
PA6.GPIOParameters=GPIO_Label
PA6.GPIO_Label=MEM_MISO
PA6.Mode=Full_Duplex_Master
PA6.Signal=SPI1_MISO
PA7.GPIOParameters=GPIO_Label
PA7.GPIO_Label=MEM_MOSI
PA7.Mode=Full_Duplex_Master
PA7.Signal=SPI1_MOSI
PA9.GPIOParameters=GPIO_Label
PA9.GPIO_Label=USB_VBUS_SENS
PA9.Mode=Activate_VBUS
PA9.Signal=USB_OTG_FS_VBUS
PB0.GPIOParameters=GPIO_Label
PB0.GPIO_Label=SOLENOID2_FB
PB0.Signal=GPIO_Input
PB1.GPIOParameters=GPIO_Label
PB1.GPIO_Label=SOLENOID3_FB
PB1.Signal=GPIO_Input
PB10.GPIOParameters=GPIO_Label
PB10.GPIO_Label=ETH_TX
PB10.Mode=Asynchronous
PB10.Signal=USART3_TX
PB11.GPIOParameters=GPIO_Label
PB11.GPIO_Label=ETH_RX
PB11.Mode=Asynchronous
PB11.Signal=USART3_RX
PB12.GPIOParameters=GPIO_Label
PB12.GPIO_Label=ETH_nRST
PB12.Signal=GPIO_Output
PB13.GPIOParameters=GPIO_Label
PB13.GPIO_Label=ETH_CTS
PB13.Mode=CTS_RTS
PB13.Signal=USART3_CTS
PB14.GPIOParameters=GPIO_Label
PB14.GPIO_Label=ETH_RTS
PB14.Mode=CTS_RTS
PB14.Signal=USART3_RTS
PB15.GPIOParameters=GPIO_Label
PB15.GPIO_Label=ETH_CP2
PB15.Signal=GPIO_Output
PB2/BOOT1.GPIOParameters=GPIO_Label
PB2/BOOT1.GPIO_Label=SOLENOID4_FB
PB2/BOOT1.Signal=GPIO_Input
PB3.GPIOParameters=GPIO_Label
PB3.GPIO_Label=MCU_TDO
PB3.Mode=JTAG_4_pins
PB3.Signal=SYS_JTDO-SWO
PB6.GPIOParameters=GPIO_Label
PB6.GPIO_Label=MAG_INT
PB6.Signal=GPIO_Output
PB7.GPIOParameters=GPIO_Label
PB7.GPIO_Label=MAG_SDA
PB7.Mode=I2C
PB7.Signal=I2C1_SDA
PB8.GPIOParameters=GPIO_Label
PB8.GPIO_Label=MAG_SCL
PB8.Mode=I2C
PB8.Signal=I2C1_SCL
PC0.GPIOParameters=GPIO_Label
PC0.GPIO_Label=PT1
PC0.Signal=ADCx_IN10
PC1.GPIOParameters=GPIO_Label
PC1.GPIO_Label=PT2
PC1.Signal=ADCx_IN11
PC10.GPIOParameters=GPIO_Label
PC10.GPIO_Label=TC0_SCK
PC10.Mode=RX_Only_Simplex_Unidirect_Master
PC10.Signal=SPI3_SCK
PC11.GPIOParameters=GPIO_Label
PC11.GPIO_Label=TC0_MISO
PC11.Mode=RX_Only_Simplex_Unidirect_Master
PC11.Signal=SPI3_MISO
PC12.GPIOParameters=GPIO_Label
PC12.GPIO_Label=TC0_nCS
PC12.Signal=GPIO_Output
PC2.GPIOParameters=GPIO_Label
PC2.GPIO_Label=PT3
PC2.Signal=ADCx_IN12
PC3.GPIOParameters=GPIO_Label
PC3.GPIO_Label=PT4
PC3.Signal=ADCx_IN13
PC4.GPIOParameters=GPIO_Label
PC4.GPIO_Label=SOLENOID0_FB
PC4.Signal=GPIO_Input
PC5.GPIOParameters=GPIO_Label
PC5.GPIO_Label=SOLENOID1_FB
PC5.Signal=GPIO_Input
PD0.GPIOParameters=GPIO_Label
PD0.GPIO_Label=TC1_nCS
PD0.Signal=GPIO_Output
PD10.GPIOParameters=GPIO_Label
PD10.GPIO_Label=REDS_CH2
PD10.Signal=GPIO_Input
PD11.GPIOParameters=GPIO_Label
PD11.GPIO_Label=REDS_CH3
PD11.Signal=GPIO_Input
PD12.GPIOParameters=GPIO_Label
PD12.GPIO_Label=REDS_CH4
PD12.Signal=GPIO_Input
PD5.GPIOParameters=GPIO_Label
PD5.GPIO_Label=IMU_INT4
PD5.Signal=GPIO_Input
PD6.GPIOParameters=GPIO_Label
PD6.GPIO_Label=IMU_INT3
PD6.Signal=GPIO_Input
PD7.GPIOParameters=GPIO_Label
PD7.GPIO_Label=IMU_INT1
PD7.Signal=GPIO_Input
PD8.GPIOParameters=GPIO_Label
PD8.GPIO_Label=REDS_CH0
PD8.Signal=GPIO_Input
PD9.GPIOParameters=GPIO_Label
PD9.GPIO_Label=REDS_CH1
PD9.Signal=GPIO_Input
PE14.GPIOParameters=GPIO_Label
PE14.GPIO_Label=RADIO0_LED
PE14.Signal=GPIO_Output
PE15.GPIOParameters=GPIO_Label
PE15.GPIO_Label=RADIO1_LED
PE15.Signal=GPIO_Output
PE2.GPIOParameters=GPIO_Label
PE2.GPIO_Label=ALT_SCK
PE2.Mode=Full_Duplex_Master
PE2.Signal=SPI4_SCK
PE3.GPIOParameters=GPIO_Label
PE3.GPIO_Label=ALT_nCS
PE3.Signal=GPIO_Output
PE5.GPIOParameters=GPIO_Label
PE5.GPIO_Label=ALT_MISO
PE5.Mode=Full_Duplex_Master
PE5.Signal=SPI4_MISO
PE6.GPIOParameters=GPIO_Label
PE6.GPIO_Label=ALT_MOSI
PE6.Mode=Full_Duplex_Master
PE6.Signal=SPI4_MOSI
PE9.GPIOParameters=GPIO_Label
PE9.GPIO_Label=ALARM
PE9.Signal=S_TIM1_CH1
PF0.GPIOParameters=GPIO_Label
PF0.GPIO_Label=RADIO_DIO1
PF0.Signal=GPIO_Output
PF1.GPIOParameters=GPIO_Label
PF1.GPIO_Label=RADIO_DIO0
PF1.Signal=GPIO_Output
PF10.GPIOParameters=GPIO_Label
PF10.GPIO_Label=PT0
PF10.Mode=IN8
PF10.Signal=ADC3_IN8
PF11.GPIOParameters=GPIO_Label
PF11.GPIO_Label=MEM1_nCS
PF11.Signal=GPIO_Output
PF13.GPIOParameters=GPIO_Label
PF13.GPIO_Label=SOLENOID0_EN
PF13.Signal=GPIO_Output
PF14.GPIOParameters=GPIO_Label
PF14.GPIO_Label=SOLENOID1_EN
PF14.Signal=GPIO_Output
PF15.GPIOParameters=GPIO_Label
PF15.GPIO_Label=SOLENOID2_EN
PF15.Signal=GPIO_Output
PF2.GPIOParameters=GPIO_Label
PF2.GPIO_Label=RADIO1_DIO1
PF2.Signal=GPIO_Output
PF3.GPIOParameters=GPIO_Label
PF3.GPIO_Label=ECU_GS
PF3.Mode=IN9
PF3.Signal=ADC3_IN9
PF4.GPIOParameters=GPIO_Label
PF4.GPIO_Label=RADIO1_nCS
PF4.Signal=GPIO_Output
PF5.GPIOParameters=GPIO_Label
PF5.GPIO_Label=RADIO1_nRST
PF5.Signal=GPIO_Output
PF6.GPIOParameters=GPIO_Label
PF6.GPIO_Label=RADIO_nCS
PF6.Signal=GPIO_Output
PF7.GPIOParameters=GPIO_Label
PF7.GPIO_Label=RADIO_SCK
PF7.Mode=Full_Duplex_Master
PF7.Signal=SPI5_SCK
PF8.GPIOParameters=GPIO_Label
PF8.GPIO_Label=RADIO_MISO
PF8.Mode=Full_Duplex_Master
PF8.Signal=SPI5_MISO
PF9.GPIOParameters=GPIO_Label
PF9.GPIO_Label=RADIO_MOSI
PF9.Mode=Full_Duplex_Master
PF9.Signal=SPI5_MOSI
PG0.GPIOParameters=GPIO_Label
PG0.GPIO_Label=SOLENOID3_EN
PG0.Signal=GPIO_Output
PG1.GPIOParameters=GPIO_Label
PG1.GPIO_Label=SOLENOID4_EN
PG1.Signal=GPIO_Output
PG10.GPIOParameters=GPIO_Label
PG10.GPIO_Label=IMU_nCS2
PG10.Signal=GPIO_Output
PG11.GPIOParameters=GPIO_Label
PG11.GPIO_Label=IMU_nCS1
PG11.Signal=GPIO_Output
PG12.GPIOParameters=GPIO_Label
PG12.GPIO_Label=IMU_MISO
PG12.Mode=Full_Duplex_Master
PG12.Signal=SPI6_MISO
PG13.GPIOParameters=GPIO_Label
PG13.GPIO_Label=IMU_SCK
PG13.Mode=Full_Duplex_Master
PG13.Signal=SPI6_SCK
PG14.GPIOParameters=GPIO_Label
PG14.GPIO_Label=IMU_MOSI
PG14.Mode=Full_Duplex_Master
PG14.Signal=SPI6_MOSI
PG5.GPIOParameters=GPIO_Label
PG5.GPIO_Label=STATUS_LED
PG5.Signal=GPIO_Output
PG9.GPIOParameters=GPIO_Label
PG9.GPIO_Label=IMU_INT2
PG9.Signal=GPIO_Output
PH0/OSC_IN.Mode=HSE-External-Clock-Source
PH0/OSC_IN.Signal=RCC_OSC_IN
PH1/OSC_OUT.Mode=HSE-External-Clock-Source
PH1/OSC_OUT.Signal=RCC_OSC_OUT
PH2.GPIOParameters=GPIO_Label
PH2.GPIO_Label=GPS_INT
PH2.Signal=GPIO_Output
PH3.GPIOParameters=GPIO_Label
PH3.GPIO_Label=MEM_nCS
PH3.Signal=GPIO_Output
PH4.Signal=GPIO_Output
PI11.GPIOParameters=GPIO_Label
PI11.GPIO_Label=RADIO_nRST
PI11.Signal=GPIO_Output
RCC.HSE_VALUE=16000000
RCC.SYSCLKFreq_VALUE=168000000
RCC.SYSCLKSource=RCC_SYSCLKSOURCE_PLLCLK
board=custom

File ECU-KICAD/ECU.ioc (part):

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Mcu.Name=STM32F469IITx
Mcu.Package=LQFP176
Mcu.UserName=STM32F469IITx
PA0/WKUP.GPIOParameters=GPIO_Label
PA0/WKUP.GPIO_Label=GPS_TX
PA0/WKUP.Mode=Asynchronous
PA0/WKUP.Signal=UART4_TX
PA1.GPIOParameters=GPIO_Label
PA1.GPIO_Label=GPS_RX
PA1.Mode=Asynchronous
PA1.Signal=UART4_RX
PA11.Mode=Device_Only
PA11.Signal=USB_OTG_FS_DM
PA12.Mode=Device_Only
PA12.Signal=USB_OTG_FS_DP
PA13.Mode=JTAG_4_pins
PA13.Signal=SYS_JTMS-SWDIO
PA14.Mode=JTAG_4_pins
PA14.Signal=SYS_JTCK-SWCLK
PA15.Mode=JTAG_4_pins
PA15.Signal=SYS_JTDI
PA2.GPIOParameters=GPIO_Label
PA2.GPIO_Label=PT5
PA2.Signal=ADCx_IN2
PA3.GPIOParameters=GPIO_Label
PA3.GPIO_Label=PT6
PA3.Signal=ADCx_IN3
PA4.GPIOParameters=GPIO_Label
PA4.GPIO_Label=ECU_BV
PA4.Signal=ADCx_IN4
PA5.GPIOParameters=GPIO_Label
PA5.GPIO_Label=MEM_SCK
PA5.Mode=Full_Duplex_Master
PA5.Signal=SPI1_SCK
PA6.GPIOParameters=GPIO_Label
PA6.GPIO_Label=MEM_MISO
PA6.Mode=Full_Duplex_Master
PA6.Signal=SPI1_MISO
PA7.GPIOParameters=GPIO_Label
PA7.GPIO_Label=MEM_MOSI
PA7.Mode=Full_Duplex_Master
PA7.Signal=SPI1_MOSI
PA9.GPIOParameters=GPIO_Label
PA9.GPIO_Label=VBUS_SENS
PA9.Mode=Activate_VBUS
PA9.Signal=USB_OTG_FS_VBUS
PB0.GPIOParameters=GPIO_Label
PB0.GPIO_Label=SOLENOID2_FB
PB0.Signal=GPIO_Input
PB1.GPIOParameters=GPIO_Label
PB1.GPIO_Label=SOLENOID3_FB
PB1.Signal=GPIO_Input
PB10.GPIOParameters=GPIO_Label
PB10.GPIO_Label=ETH_TX
PB10.Mode=Asynchronous
PB10.Signal=USART3_TX
PB11.GPIOParameters=GPIO_Label
PB11.GPIO_Label=ETH_RX
PB11.Mode=Asynchronous
PB11.Signal=USART3_RX
PB12.GPIOParameters=GPIO_Label
PB12.GPIO_Label=ETH_nRST
PB12.Signal=GPIO_Output
PB13.GPIOParameters=GPIO_Label
PB13.GPIO_Label=ETH_CTS
PB13.Mode=CTS_RTS
PB13.Signal=USART3_CTS
PB14.GPIOParameters=GPIO_Label
PB14.GPIO_Label=ETH_RTS
PB14.Mode=CTS_RTS
PB14.Signal=USART3_RTS
PB15.GPIOParameters=GPIO_Label
PB15.GPIO_Label=ETH_CP2
PB15.Signal=GPIO_Input
PB3.Mode=JTAG_4_pins
PB3.Signal=SYS_JTDO-SWO
PB6.GPIOParameters=GPIO_Label
PB6.GPIO_Label=MAG_INT
PB6.Signal=GPIO_Input
PB7.GPIOParameters=GPIO_Label
PB7.GPIO_Label=MAG_SDA
PB7.Mode=I2C
PB7.Signal=I2C1_SDA
PB8.GPIOParameters=GPIO_Label
PB8.GPIO_Label=MAG_SCL
PB8.Mode=I2C
PB8.Signal=I2C1_SCL
PC0.GPIOParameters=GPIO_Label
PC0.GPIO_Label=PT1
PC0.Signal=ADCx_IN10
PC1.GPIOParameters=GPIO_Label
PC1.GPIO_Label=PT2
PC1.Signal=ADCx_IN11
PC10.GPIOParameters=GPIO_Label
PC10.GPIO_Label=TC0_SCK
PC10.Mode=RX_Only_Simplex_Unidirect_Master
PC10.Signal=SPI3_SCK
PC11.GPIOParameters=GPIO_Label
PC11.GPIO_Label=TC0_MISO
PC11.Mode=RX_Only_Simplex_Unidirect_Master
PC11.Signal=SPI3_MISO
PC12.GPIOParameters=GPIO_Label
PC12.GPIO_Label=TC0_nCS
PC12.Signal=GPIO_Output
PC2.GPIOParameters=GPIO_Label
PC2.GPIO_Label=PT3
PC2.Signal=ADCx_IN12
PC3.GPIOParameters=GPIO_Label
PC3.GPIO_Label=PT4
PC3.Signal=ADCx_IN13
PC4.GPIOParameters=GPIO_Label
PC4.GPIO_Label=SOLENOID0_FB
PC4.Signal=GPIO_Input
PC5.GPIOParameters=GPIO_Label
PC5.GPIO_Label=SOLENOID1_FB
PC5.Signal=GPIO_Input
PD0.GPIOParameters=GPIO_Label
PD0.GPIO_Label=TC1_nCS
PD0.Signal=GPIO_Output
PD10.GPIOParameters=GPIO_Label
PD10.GPIO_Label=REDs_CH2
PD10.Signal=GPIO_Input
PD11.GPIOParameters=GPIO_Label
PD11.GPIO_Label=REDs_CH3
PD11.Signal=GPIO_Input
PD12.GPIOParameters=GPIO_Label
PD12.GPIO_Label=REDs_CH4
PD12.Signal=GPIO_Input
PD5.GPIOParameters=GPIO_Label
PD5.GPIO_Label=IMU_INT4
PD5.Signal=GPIO_Input
PD6.GPIOParameters=GPIO_Label
PD6.GPIO_Label=IMU_INT3
PD6.Signal=GPIO_Input
PD7.GPIOParameters=GPIO_Label
PD7.GPIO_Label=IMU_INT1
PD7.Signal=GPIO_Input
PD8.GPIOParameters=GPIO_Label
PD8.GPIO_Label=REDs-CH0
PD8.Signal=GPIO_Input
PD9.GPIOParameters=GPIO_Label
PD9.GPIO_Label=REDs_CH1
PD9.Signal=GPIO_Input
PE14.GPIOParameters=GPIO_Label
PE14.GPIO_Label=RADIO0_LED
PE14.Signal=GPIO_Output
PE15.GPIOParameters=GPIO_Label
PE15.GPIO_Label=RADIO1_LED
PE15.Signal=GPIO_Output
PE2.GPIOParameters=GPIO_Label
PE2.GPIO_Label=ALT_SCK
PE2.Mode=Full_Duplex_Master
PE2.Signal=SPI4_SCK
PE3.GPIOParameters=GPIO_Label
PE3.GPIO_Label=ALT_nCS
PE3.Signal=GPIO_Output
PE5.GPIOParameters=GPIO_Label
PE5.GPIO_Label=ALT_MISO
PE5.Mode=Full_Duplex_Master
PE5.Signal=SPI4_MISO
PE6.GPIOParameters=GPIO_Label
PE6.GPIO_Label=ALT_MOSI
PE6.Mode=Full_Duplex_Master
PE6.Signal=SPI4_MOSI
PE9.GPIOParameters=GPIO_Label
PE9.GPIO_Label=ALARM
PE9.Signal=S_TIM1_CH1
PF0.GPIOParameters=GPIO_Label
PF0.GPIO_Label=RADIO_DIO1
PF0.Signal=GPIO_Input
PF1.GPIOParameters=GPIO_Label
PF1.GPIO_Label=RADIO_DIO0
PF1.Signal=GPIO_Input
PF10.GPIOParameters=GPIO_Label
PF10.GPIO_Label=PT0
PF10.Mode=IN8
PF10.Signal=ADC3_IN8
PF11.GPIOParameters=GPIO_Label
PF11.GPIO_Label=MEM1_nCS
PF11.Signal=GPIO_Output
PF13.GPIOParameters=GPIO_Label
PF13.GPIO_Label=SOLENOID0_EN
PF13.Signal=GPIO_Output
PF14.GPIOParameters=GPIO_Label
PF14.GPIO_Label=SOLENOID1_EN
PF14.Signal=GPIO_Output
PF15.GPIOParameters=GPIO_Label
PF15.GPIO_Label=SOLENOID2_EN
PF15.Signal=GPIO_Output
PF2.GPIOParameters=GPIO_Label
PF2.GPIO_Label=RADIO1_DIO1
PF2.Signal=GPIO_Input
PF3.GPIOParameters=GPIO_Label
PF3.GPIO_Label=ECU_GS
PF3.Mode=IN9
PF3.Signal=ADC3_IN9
PF4.GPIOParameters=GPIO_Label
PF4.GPIO_Label=RADIO1_nCS
PF4.Signal=GPIO_Output
PF5.GPIOParameters=GPIO_Label
PF5.GPIO_Label=RADIO1_nRST
PF5.Signal=GPIO_Output
PF6.GPIOParameters=GPIO_Label
PF6.GPIO_Label=RADIO_nCS
PF6.Signal=GPIO_Output
PF7.GPIOParameters=GPIO_Label
PF7.GPIO_Label=RADIO_SCK
PF7.Mode=Full_Duplex_Master
PF7.Signal=SPI5_SCK
PF8.GPIOParameters=GPIO_Label
PF8.GPIO_Label=RADIO_MISO
PF8.Mode=Full_Duplex_Master
PF8.Signal=SPI5_MISO
PF9.GPIOParameters=GPIO_Label
PF9.GPIO_Label=RADIO_MOSI
PF9.Mode=Full_Duplex_Master
PF9.Signal=SPI5_MOSI
PG0.GPIOParameters=GPIO_Label
PG0.GPIO_Label=SOLENOID3_EN
PG0.Signal=GPIO_Input
PG1.GPIOParameters=GPIO_Label
PG1.GPIO_Label=SOLENOID4_EN
PG1.Signal=GPIO_Output
PG10.GPIOParameters=GPIO_Label
PG10.GPIO_Label=IMU_nCS2
PG10.Signal=GPIO_Output
PG11.GPIOParameters=GPIO_Label
PG11.GPIO_Label=IMU_nCS1
PG11.Signal=GPIO_Output
PG12.GPIOParameters=GPIO_Label
PG12.GPIO_Label=IMU_MISO
PG12.Mode=Full_Duplex_Master
PG12.Signal=SPI6_MISO
PG13.GPIOParameters=GPIO_Label
PG13.GPIO_Label=IMU_SCK
PG13.Mode=Full_Duplex_Master
PG13.Signal=SPI6_SCK
PG14.GPIOParameters=GPIO_Label
PG14.GPIO_Label=IMU_MOSI
PG14.Mode=Full_Duplex_Master
PG14.Signal=SPI6_MOSI
PG5.GPIOParameters=GPIO_Label
PG5.GPIO_Label=STATUS_LED
PG5.Signal=GPIO_Output
PG9.GPIOParameters=GPIO_Label
PG9.GPIO_Label=IMU_INT2
PG9.Signal=GPIO_Input
PH0/OSC_IN.Mode=HSE-External-Oscillator
PH0/OSC_IN.Signal=RCC_OSC_IN
PH1/OSC_OUT.Mode=HSE-External-Oscillator
PH1/OSC_OUT.Signal=RCC_OSC_OUT
PH2.GPIOParameters=GPIO_Label
PH2.GPIO_Label=GPS_INT
PH2.Signal=GPIO_Input
PH3.GPIOParameters=GPIO_Label
PH3.GPIO_Label=MEM_nCS
PH3.Signal=GPIO_Output
PI11.GPIOParameters=GPIO_Label
PI11.GPIO_Label=RADIO_nRST
PI11.Signal=GPIO_Output
RCC.HSE_VALUE=16000000
RCC.SYSCLKFreq_VALUE=16000000
RCC.SYSCLKSource=RCC_SYSCLKSOURCE_HSE
board=custom
